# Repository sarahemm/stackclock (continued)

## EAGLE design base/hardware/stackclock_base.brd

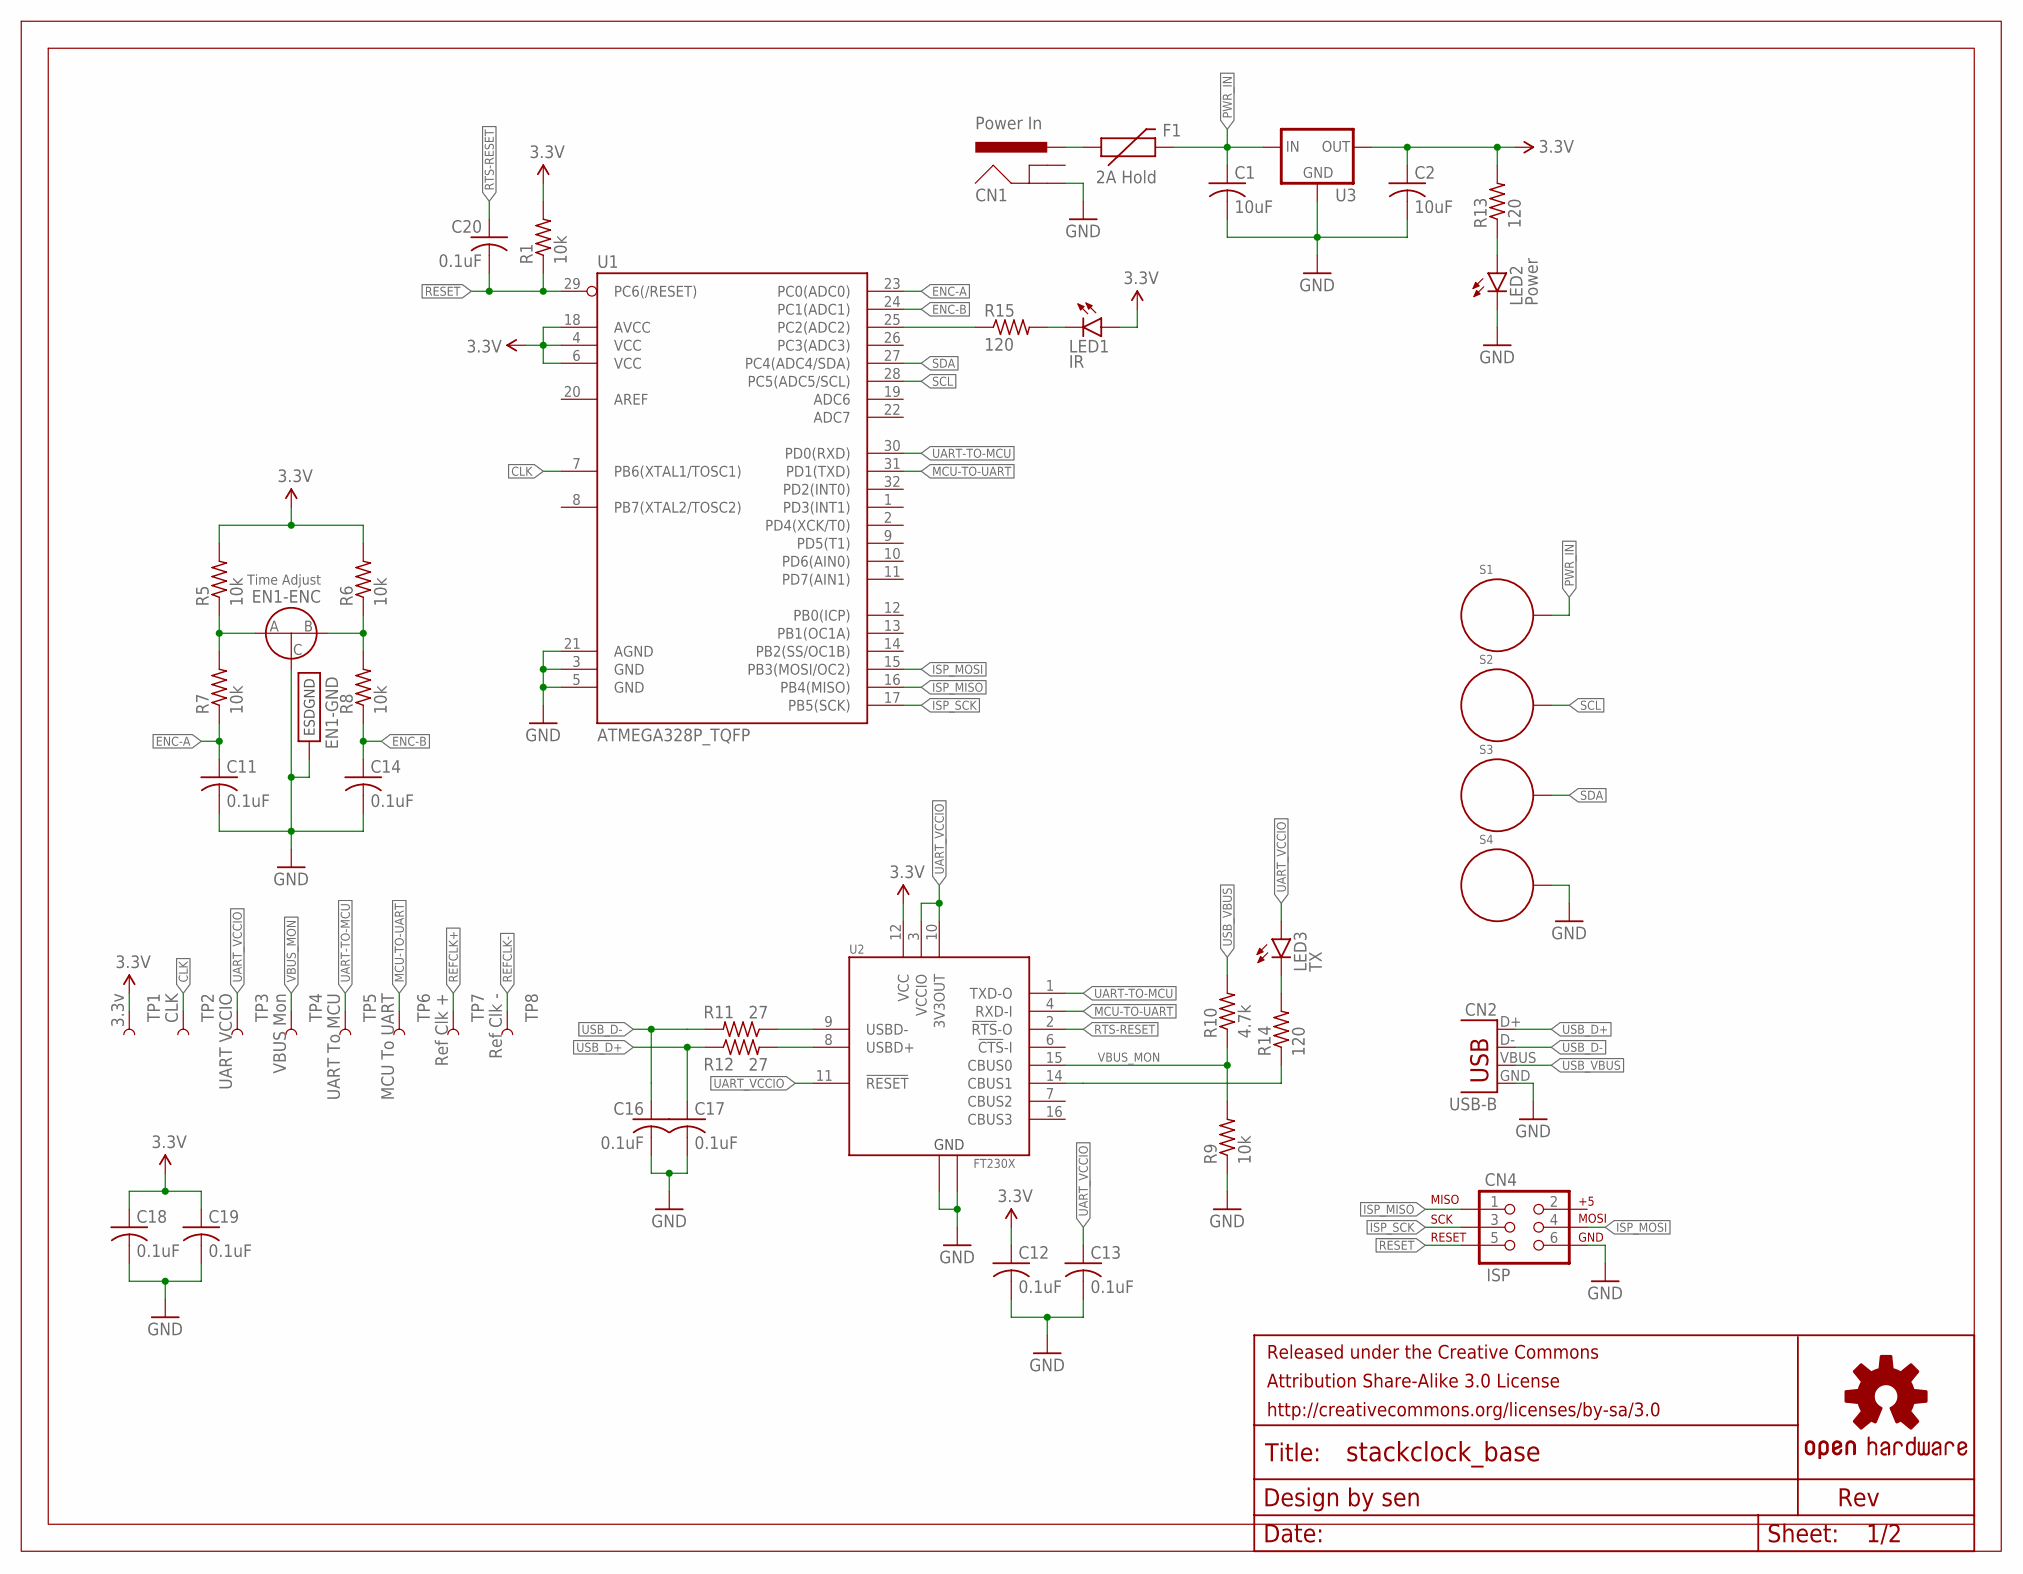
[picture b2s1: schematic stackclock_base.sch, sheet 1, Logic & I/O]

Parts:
C1, C2: 10uF; C0805
C11, C12, C13, C14, C16, C17, C18, C19, C20: 0.1uF; C0603
CN1: Power In; POWER_JACK_PTH
CN2: USB-B; USB-B-PTH
CN4: ISP; 2X3_LOCK
EN1: Time Adjust; BOURNS-PEC12R-2XXXF-N
F1: 2A Hold; PTC-1206
FRAME1: FRAME-LETTER-GRID-OSHW-SENOSHW-LOGO-L; OSHW-LOGO-L
LED1: IR; LED-1206
LED2: Power; LED-0603
LED3: TX; LED-0603
R1, R5, R6, R7, R8, R9: 10k; R0603
R10: 4.7k; R0603
R11, R12: 27; R0603
R13, R14, R15: 120; R0603
S1: VIN; STANDOFF-ELECTRICAL
S2: SCL; STANDOFF-ELECTRICAL
S3: SDA; STANDOFF-ELECTRICAL
S4: GND; STANDOFF-ELECTRICAL
TP1: 3.3v; TP_15TH
TP2: CLK; TP_15TH
TP3: UART VCCIO; TP_15TH
TP4: VBUS Mon; TP_15TH
TP5: UART To MCU; TP_15TH
TP6: MCU To UART; TP_15TH
TP7: Ref Clk +; TP_15TH
TP8: Ref Clk -; TP_15TH
U1: ATMEGA328P_TQFP; TQFP32-08
U2: FT230X; SSOP16
U3: NCP1117DT33G; DPAK

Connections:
3.3V: C2.1, C12.1, C18.1, C19.1, LED1.A, R1.2, R5.2, R6.2, R13.2, TP1.P$1, U1.4 (VCC), U1.6 (VCC), U1.18 (AVCC), U2.12 (VCC), U3.4 (OUT); also elsewhere on the board
!RESET: C20.2, CN4.5, R1.1, U1.29 (PC6(/RESET))
CLK: TP2.P$1, U1.7 (PB6(XTAL1/TOSC1)); also elsewhere on the board
DATA_LED: R14.1, U2.14 (CBUS1)
ENC-A: C11.1, R7.1, U1.23 (PC0(ADC0))
ENC-A_RAW: EN1.A, R5.1, R7.2
ENC-B: C14.1, R8.1, U1.24 (PC1(ADC1))
ENC-B_RAW: EN1.B, R6.1, R8.2
GND: C1.2, C2.2, C11.2, C12.2, C13.2, C14.2, C16.2, C17.2, C18.2, C19.2, CN1.GND, CN2.GND, CN4.6, EN1.C, EN1.SUPPORT1 (ESDGND), EN1.SUPPORT2 (ESDGND), LED2.C, R9.1, S4.P1, U1.3 (GND), U1.5 (GND), U1.21 (AGND), U2.5 (GND), U2.13 (GND), U3.1 (GND); also elsewhere on the board
IR_CTL: R15.1, U1.25 (PC2(ADC2))
IR_R: LED1.C, R15.2
ISP_MISO: CN4.1, U1.16 (PB4(MISO))
ISP_MOSI: CN4.4, U1.15 (PB3(MOSI/OC2))
ISP_SCK: CN4.3, U1.17 (PB5(SCK))
LED2_R: LED2.A, R13.1
LED3_R: LED3.C, R14.2
MCU-TO-UART: TP6.P$1, U1.31 (PD1(TXD)), U2.4 (RXD-I)
PWR_IN: C1.1, F1.2, S1.P1, U3.3 (IN)
PWR_IN_PREFUSE: CN1.PWR, F1.1
REFCLK+: TP7.P$1; also elsewhere on the board
REFCLK-: TP8.P$1; also elsewhere on the board
RTS-RESET: C20.1, U2.2 (!RTS!-O)
SCL: S2.P1, U1.28 (PC5(ADC5/SCL))
SDA: S3.P1, U1.27 (PC4(ADC4/SDA))
UART-TO-MCU: TP5.P$1, U1.30 (PD0(RXD)), U2.1 (TXD-O)
UART_VCCIO: C13.1, LED3.A, TP3.P$1, U2.3 (VCCIO), U2.10 (3V3OUT), U2.11 (!RESET)
USB_D+: C17.1, CN2.D+, R12.1
USB_D+_POSTRES: R12.2, U2.8 (USBD+)
USB_D-: C16.1, CN2.D-, R11.2
USB_D-_POSTRES: R11.1, U2.9 (USBD-)
USB_VBUS: CN2.VBUS, R10.2
VBUS_MON: R9.2, R10.1, TP4.P$1, U2.15 (CBUS0)

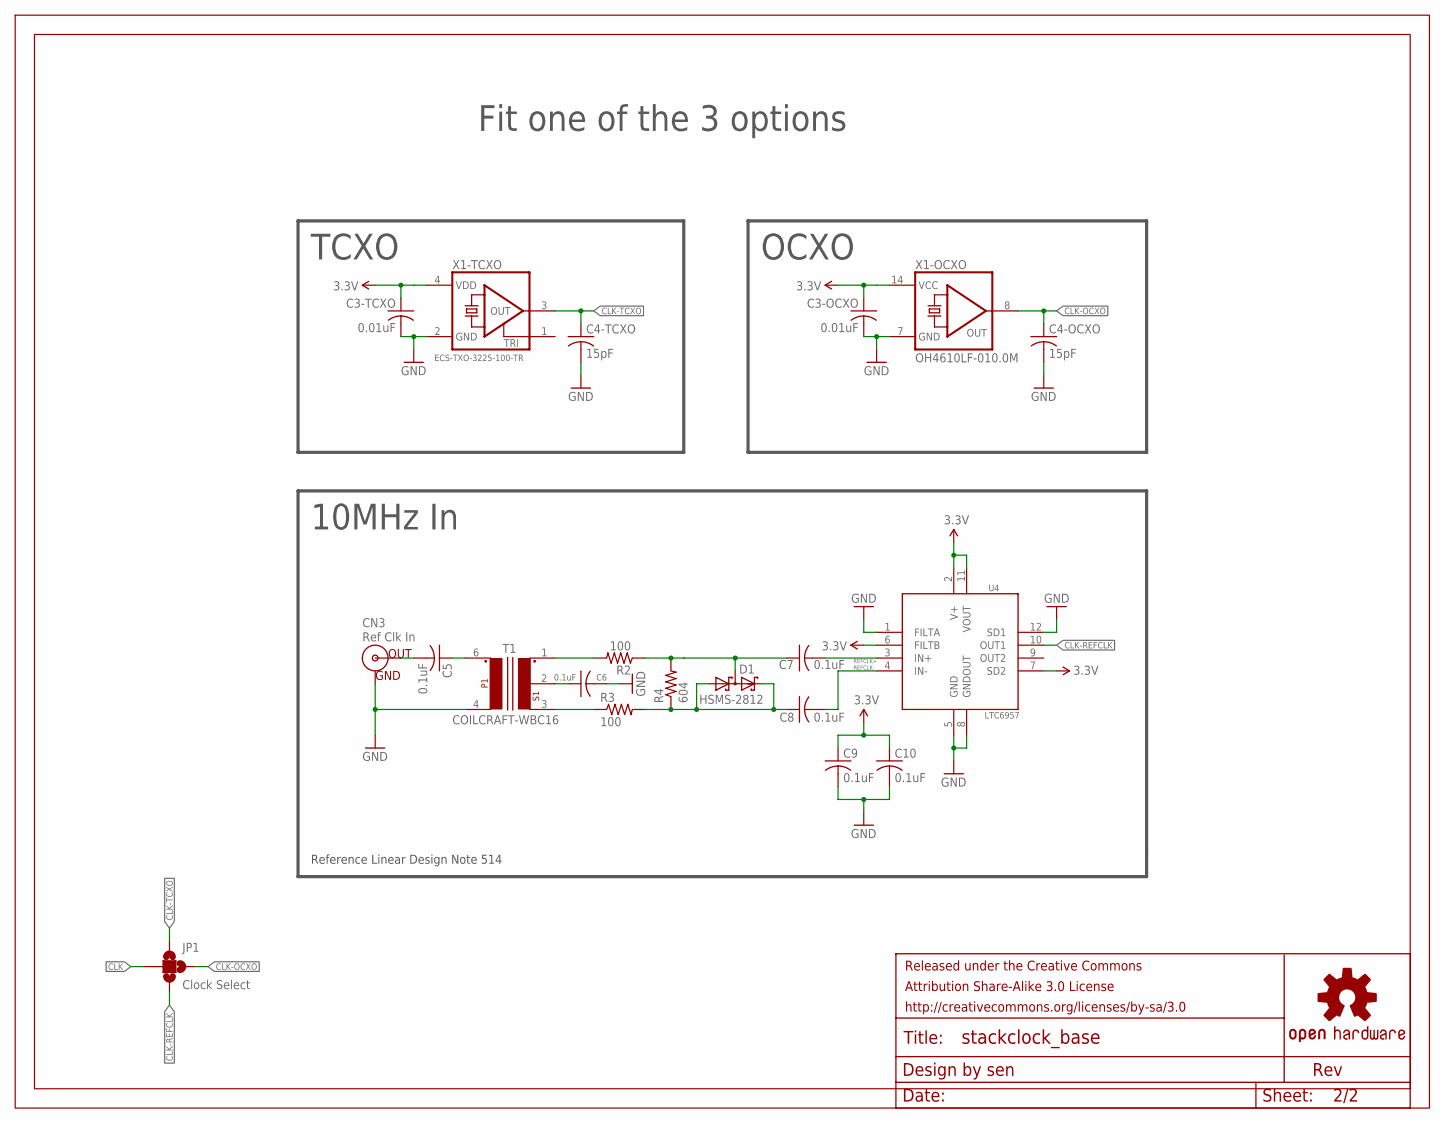
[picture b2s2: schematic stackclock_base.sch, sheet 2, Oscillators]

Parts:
C3-OCXO, C3-TCXO: 0.01uF; C0603
C4-OCXO, C4-TCXO: 15pF; C0603
C5, C6, C7, C8, C9, C10: 0.1uF; C0603
CN3: Ref Clk In; BNC
D1: HSMS-2812; SOT23
FRAME2: FRAME-LETTER-GRID-OSHW-SENOSHW-LOGO-L; OSHW-LOGO-L
JP1: Clock Select; PAD-JUMPER-4-NO_YES_SILK
R2, R3: 100; R0603
R4: 604; R0603
T1: COILCRAFT-WBC16; COILCRAFT-WBC
U4: LTC6957; MSOP12
X1-OCXO: OH4610LF-010.0M; DIL14S
X1-TCXO: ECS-TXO-3225-100-TR; ASE

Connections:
3.3V: C3-OCXO.1, C3-TCXO.1, C9.1, C10.1, U4.2 (V+), U4.6 (FILTB), U4.7 (SD2), U4.11 (VOUT), X1-OCXO.14 (VCC), X1-TCXO.4 (VDD); also elsewhere on the board
CLK: JP1.C; also elsewhere on the board
CLK-OCXO: C4-OCXO.1, JP1.3, X1-OCXO.8 (OUT)
CLK-REFCLK: JP1.2, U4.10 (OUT1)
CLK-TCXO: C4-TCXO.1, JP1.1, X1-TCXO.3 (OUT)
GND: C3-OCXO.2, C3-TCXO.2, C4-OCXO.2, C4-TCXO.2, C6.2, C9.2, C10.2, CN3.GND, T1.4 (PRI-2), U4.1 (FILTA), U4.5 (GND), U4.8 (GNDOUT), U4.12 (SD1), X1-OCXO.7 (GND), X1-TCXO.2 (GND); also elsewhere on the board
REFCLK+: C7.2, U4.3 (IN+); also elsewhere on the board
REFCLK+-POSTTRANS: R2.2, T1.1 (SEC-1)
REFCLK+-PRECAP: C7.1, D1.3 (C1A2), R2.1, R4.2
REFCLK-: C8.2, U4.4 (IN-); also elsewhere on the board
REFCLK--POSTTRANS: R3.1, T1.3 (SEC-2)
REFCLK--PRECAP: C8.1, D1.1 (A1), D1.2 (C2), R3.2, R4.1
REFCLK-CTRTAP: C6.1, T1.2 (SEC-CT)
REFCLK_IN: C5.2, CN3.S (OUT)
REFCLK_PRETRANS: C5.1, T1.6 (PRI-1)

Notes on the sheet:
10MHz In
TCXO
OCXO
Fit one of the 3 options
Reference Linear Design Note 514

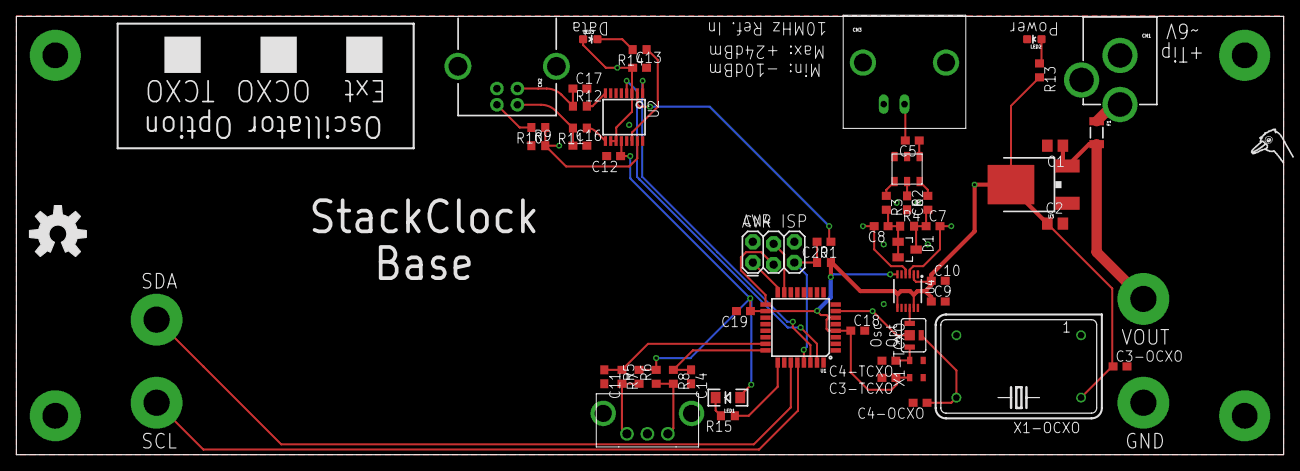
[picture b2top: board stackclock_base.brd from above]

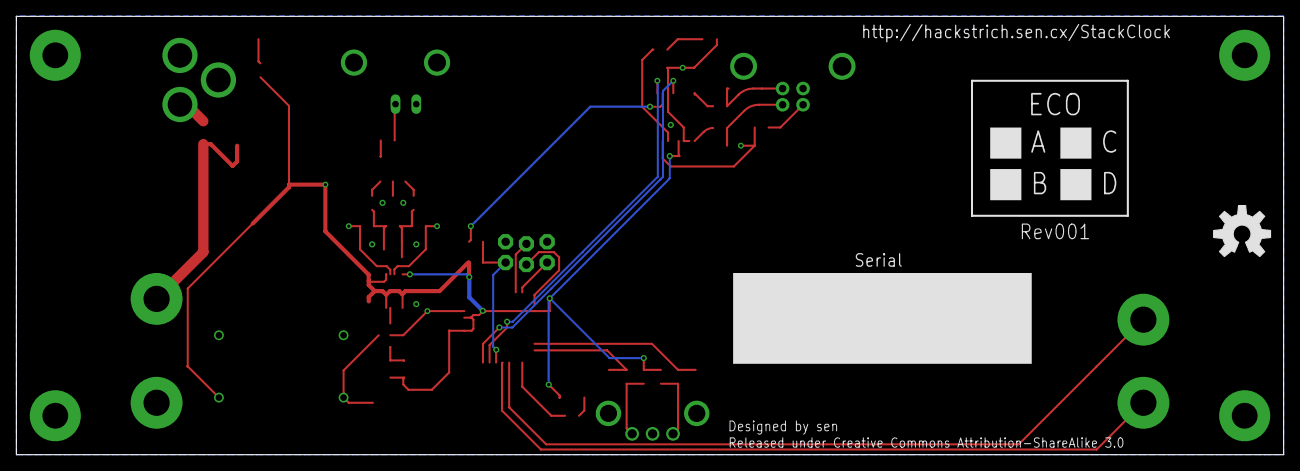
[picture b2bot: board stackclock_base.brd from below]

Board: 2 copper layers, 154.9 x 53.6 mm, 69 parts (9 on the bottom side), 42 nets.

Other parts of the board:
U$1: STRICH-LOGO

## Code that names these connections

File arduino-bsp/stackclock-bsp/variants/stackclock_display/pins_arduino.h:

/*
  pins_arduino.h - Pin definition functions for Arduino
  Part of Arduino - http://www.arduino.cc/

  Copyright (c) 2007 David A. Mellis

  This library is free software; you can redistribute it and/or
  modify it under the terms of the GNU Lesser General Public
  License as published by the Free Software Foundation; either
  version 2.1 of the License, or (at your option) any later version.

  This library is distributed in the hope that it will be useful,
  but WITHOUT ANY WARRANTY; without even the implied warranty of
  MERCHANTABILITY or FITNESS FOR A PARTICULAR PURPOSE.  See the GNU
  Lesser General Public License for more details.

  You should have received a copy of the GNU Lesser General
  Public License along with this library; if not, write to the
  Free Software Foundation, Inc., 59 Temple Place, Suite 330,
  Boston, MA  02111-1307  USA
*/

#ifndef Pins_Arduino_h
#define Pins_Arduino_h

#include <avr/pgmspace.h>

#define NUM_DIGITAL_PINS            24
#define NUM_ANALOG_INPUTS           8
#define analogInputToDigitalPin(p)  ((p < 8) ? (p) + 14 : -1)

# define digitalPinHasPWM(p) ((p) == 0 || (p) == 1 || (p) == 2 || (p) == 3 || (p) == 5 || (p) == 6 || (p) == 9 || (p) == 10 || (p) == 11)

#define PIN_SPI_SS    (10)
#define PIN_SPI_MOSI  (11)
#define PIN_SPI_MISO  (12)
#define PIN_SPI_SCK   (13)

static const uint8_t SS   = PIN_SPI_SS;
static const uint8_t MOSI = PIN_SPI_MOSI;
static const uint8_t MISO = PIN_SPI_MISO;
static const uint8_t SCK  = PIN_SPI_SCK;

#define PIN_WIRE_SDA        (18)
#define PIN_WIRE_SCL        (19)

static const uint8_t SDA = PIN_WIRE_SDA;
static const uint8_t SCL = PIN_WIRE_SCL;

#define PIN_WIRE1_SDA   (20)
#define PIN_WIRE1_SCL   (21)

static const uint8_t SDA1 = PIN_WIRE1_SDA;
static const uint8_t SCL1 = PIN_WIRE1_SCL;

#define LED_BUILTIN 13

#define PIN_A0   (14)
#define PIN_A1   (15)
#define PIN_A2   (16)
#define PIN_A3   (17)
#define PIN_A4   (18)
#define PIN_A5   (19)
#define PIN_A6   (20)
#define PIN_A7   (21)

static const uint8_t A0 = PIN_A0;
static const uint8_t A1 = PIN_A1;
static const uint8_t A2 = PIN_A2;
static const uint8_t A3 = PIN_A3;
static const uint8_t A4 = PIN_A4;
static const uint8_t A5 = PIN_A5;
static const uint8_t A6 = PIN_A6;
static const uint8_t A7 = PIN_A7;

#define digitalPinToPCICR(p)    (((p) >= 0 && (p) <= 23) ? (&PCICR) : ((uint8_t *)0))
#define digitalPinToPCICRbit(p) (((p) <= 7) ? 2 : (((p) <= 13) ? 0 : 1))
#define digitalPinToPCMSK(p)    (((p) <= 7) ? (&PCMSK2) : (((p) <= 13) ? (&PCMSK0) : (((p) <= 23) ? (&PCMSK1) : ((uint8_t *)0))))
#define digitalPinToPCMSKbit(p) (((p) <= 7) ? (p) : (((p) <= 13) ? ((p) - 8) : ((p) - 14)))

#define digitalPinToInterrupt(p)  ((p) == 2 ? 0 : ((p) == 3 ? 1 : NOT_AN_INTERRUPT))

#ifdef ARDUINO_MAIN

// these arrays map port names (e.g. port B) to the
// appropriate addresses for various functions (e.g. reading
// and writing)
const uint16_t PROGMEM port_to_mode_PGM[] = {
	NOT_A_PORT,
	NOT_A_PORT,
	(uint16_t) &DDRB,
	(uint16_t) &DDRC,
	(uint16_t) &DDRD,
	(uint16_t) &DDRE,
};

const uint16_t PROGMEM port_to_output_PGM[] = {
	NOT_A_PORT,
	NOT_A_PORT,
	(uint16_t) &PORTB,
	(uint16_t) &PORTC,
	(uint16_t) &PORTD,
	(uint16_t) &PORTE,
};

const uint16_t PROGMEM port_to_input_PGM[] = {
	NOT_A_PORT,
	NOT_A_PORT,
	(uint16_t) &PINB,
	(uint16_t) &PINC,
	(uint16_t) &PIND,
	(uint16_t) &PINE,
};

const uint8_t PROGMEM digital_pin_to_port_PGM[] = {
	PD, /* 0 */
	PD,
	PD,
	PD,
	PD,
	PD,
	PD,
	PD,
	PB, /* 8 */
	PB,
	PB,
	PB,
	PB,
	PB,
	PC, /* 14 */
	PC,
	PC,
	PC,
	PC,
	PC,
	PE, /* 20 */
	PE,
	PE,
	PE,
};

const uint8_t PROGMEM digital_pin_to_bit_mask_PGM[] = {
	_BV(0), /* 0, port D */
	_BV(1),
	_BV(2),
	_BV(3),
	_BV(4),
	_BV(5),
	_BV(6),
	_BV(7),
	_BV(0), /* 8, port B */
	_BV(1),
	_BV(2),
	_BV(3),
	_BV(4),
	_BV(5),
	_BV(0), /* 14, port C */
	_BV(1),
	_BV(2),
	_BV(3),
	_BV(4),
	_BV(5),
	_BV(0), /* 20, port E */
	_BV(1),
	_BV(2),
	_BV(3),
};

const uint8_t PROGMEM digital_pin_to_timer_PGM[] = {
  TIMER3A,        /* 0 - port D */
  TIMER4A,
  TIMER4B, // TIMER3B or TIMER4B
	TIMER2B,
	NOT_ON_TIMER,
	TIMER0B,
	TIMER0A,
	NOT_ON_TIMER,
	NOT_ON_TIMER, /* 8 - port B */
	TIMER1A,
	TIMER1B,
	TIMER2A,
	NOT_ON_TIMER,
	NOT_ON_TIMER,
	NOT_ON_TIMER, /* 14 - port C */
	NOT_ON_TIMER,
	NOT_ON_TIMER,
	NOT_ON_TIMER,
	NOT_ON_TIMER,
	NOT_ON_TIMER,
	NOT_ON_TIMER, /* 20 - port E */
	NOT_ON_TIMER,
	NOT_ON_TIMER,
	NOT_ON_TIMER,
};

#endif

// These serial port names are intended to allow libraries and architecture-neutral
// sketches to automatically default to the correct port name for a particular type
// of use.  For example, a GPS module would normally connect to SERIAL_PORT_HARDWARE_OPEN,
// the first hardware serial port whose RX/TX pins are not dedicated to another use.
//
// SERIAL_PORT_MONITOR        Port which normally prints to the Arduino Serial Monitor
//
// SERIAL_PORT_USBVIRTUAL     Port which is USB virtual serial
//
// SERIAL_PORT_LINUXBRIDGE    Port which connects to a Linux system via Bridge library
//
// SERIAL_PORT_HARDWARE       Hardware serial port, physical RX & TX pins.
//
// SERIAL_PORT_HARDWARE_OPEN  Hardware serial ports which are open for use.  Their RX & TX
//                            pins are NOT connected to anything by default.
#define SERIAL_PORT_MONITOR   Serial
#define SERIAL_PORT_HARDWARE  Serial

/* StackClock-specific bits here, since I can't figure out how to just extend an existing variant (standard) */
#undef LED_BUILTIN

// digital
#define PIN_DSP1_ANODE    (2)
#define PIN_DSP2_ANODE    (3)
#define PIN_DSP3_ANODE    (4)

#define PIN_DSP4_DPL      (7)
#define PIN_DSP5_DPL      (8)
#define PIN_DSP6_DPL      (9)
#define PIN_DSP7_DPL      (10)

#define PIN_LED_SDA       (20)
#define PIN_LED_SCL       (21)
#define PIN_LED_nSS       (22)
#define PIN_LED_MOSI      (23)
#define PIN_LED_SCK       (15)
#define PIN_LED_nOE       (16)

// analog
#define IR_LEVEL          (3)

// timer pins
#define TIMER1_A_PIN      (9)

#endif

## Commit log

2017-10-05 Initial work on the schematic for the base.
    Completed main schematic including TCXO, OCXO, and external reference options.
    Still need to do USB interface, IR, and diagnostics (TPs, etc.).
2017-10-11 Completed and checklisted schematic.
2017-10-11 Started routing board.
2017-10-15 Completed as much routing as possible until Display boards are done.
2017-10-22 Changed IR LED to SMD so that we can line up bottom/top easier on display boards.
2017-10-22 Adding complete/checklisted display schematic.
2017-10-23 Completed and checklisted board.
2017-10-30 Placement mostly complete, routing still in progress.
2017-11-01 Tweaked silkscreen slightly.
2017-11-02 Adding CAM and fixing via tenting on board. Ready for manufacturing.
2017-11-02 Increased slot width to meet OSH Park requirments.
2017-11-02 Added "CUT OUT" text per OSH Park requirements.
2017-11-21 Added label to Oscillator Option jumper.
2017-11-21 Moved TPs to top of board, oops.
2017-11-21 Completed CAM files.
2017-12-31 Adding beginning of board support package for Arduino.
2017-12-31 Adding test BSP for the StackClock boards.
    I hate adding ZIP files to Git, but that's what Arduino needs...
2017-12-31 Updating index with BSP zip file, hopefully.
2017-12-31 Fixing ZIP file to include one directory under the root as required.
2017-12-31 Updating checksum for updated ZIP, missed last time.
2017-12-31 Releasing BSP 1.0.1 which includes the bootloader for the Base board.
    Bootloader is just Optiboot compiled to use 115200bps and a 10Mhz clock.
2018-01-06 Releasing the StackClock BSP 1.0.2 w/ initial support for the Display board.
2018-01-07 Adding bootloader, flashing stuff, and updated pin defs for the Display board.
2018-01-07 Adding tool to turn 16-seg fonts into C arrays and the font description file itself.
2018-01-07 Adding libraries for Wire/SPI from wattuino, BSP release 1.0.4.
2018-01-07 Adding current firmware for the Base and Display boards.
2018-02-18 Fixed duplicate definition of PIN_DSP6_DPL and missing PIN_DSP7_DPL.
2018-02-18 Making BSP compatibile with toolchain 1.6.205.
2018-02-18 Fixing incorrect pins for SCL1 and SDA1. BSP release 1.0.6.
2018-02-18 Adding missing 1.0.6 ZIP.
2018-02-19 Adding the 7-segment font definition.
2018-02-19 Adding note about being used for both alpha and numeric fonts.
2018-02-19 Split display code up into various modules. Not tested on hardware yet.
2018-02-19 Fixing bug where address was being sent instead of command.
2018-02-19 Adding missing header file for stack commands.
2018-03-01 Moved stack init code into Stack module.
2018-03-02 Stabilized existing codebase, both Base and Display now work and talk to each other in test mode.
2018-03-03 Started work on Rev002.
2018-03-04 Completed Rev002 Display board, pending checklisting.
2018-03-07 Fixed numerous bugs and implemented Time module, now keeps (mostly) time!
2018-03-07 Fixed numerous bugs, still some lurking as the display gets corrupted for one second randomly.
2018-03-07 Committing final Rev002, ready to go to PCB manufacturing.
2018-03-08 Added version resistor and ECO silkscreen, now final Rev002, submitted for mfg.
2019-01-12 A couple minor optimizations.
2019-01-12 Give the display boards 250ms to initialize before talking to them.
2019-01-12 New BSP release to add timer pin for display board.
2019-01-12 Removed no longer required debug prints.
2019-01-12 Changed alpha muxing to be timer-based rather than manual.
    Now using TimerOne library and the alphaRefreshDisplays function switches which digit is being displayed each time it is called. Much more stable display now, no matter what else is going on or how b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
